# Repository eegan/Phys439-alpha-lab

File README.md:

# Phys439-alpha-lab
Arduino code and KiCAD schematic for McGill PHYS 439 lab setup

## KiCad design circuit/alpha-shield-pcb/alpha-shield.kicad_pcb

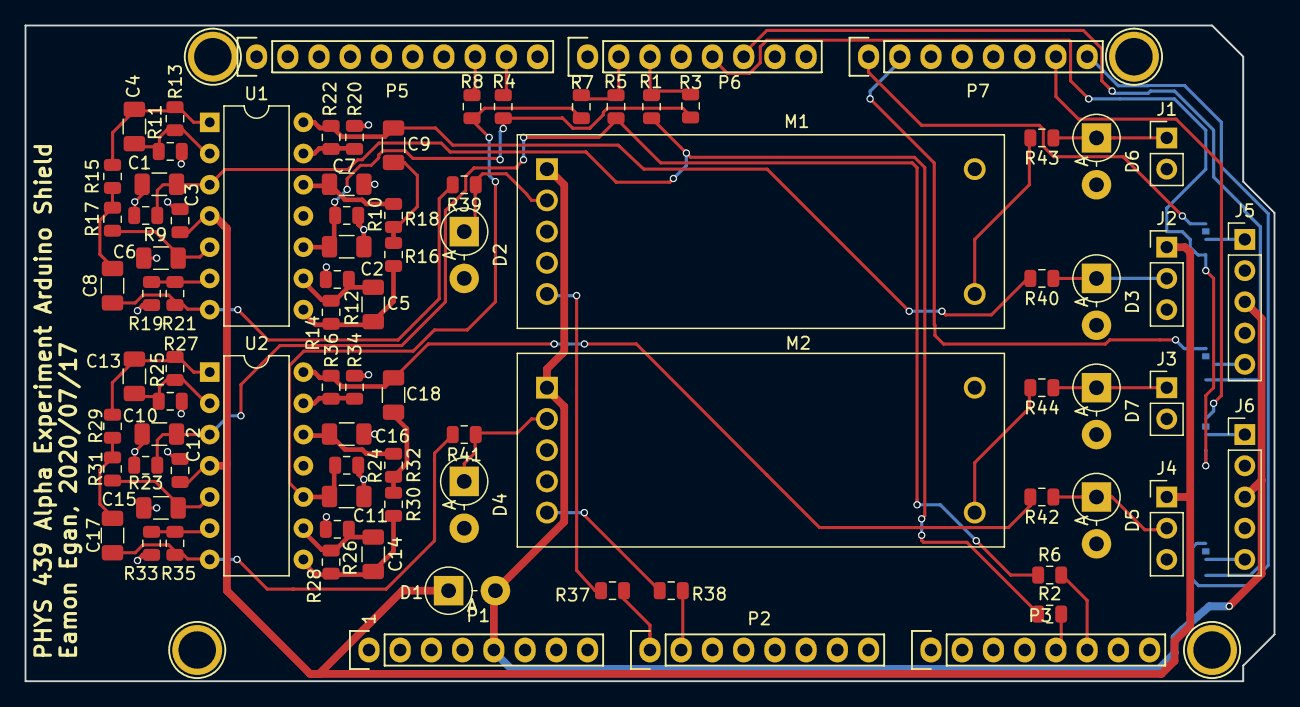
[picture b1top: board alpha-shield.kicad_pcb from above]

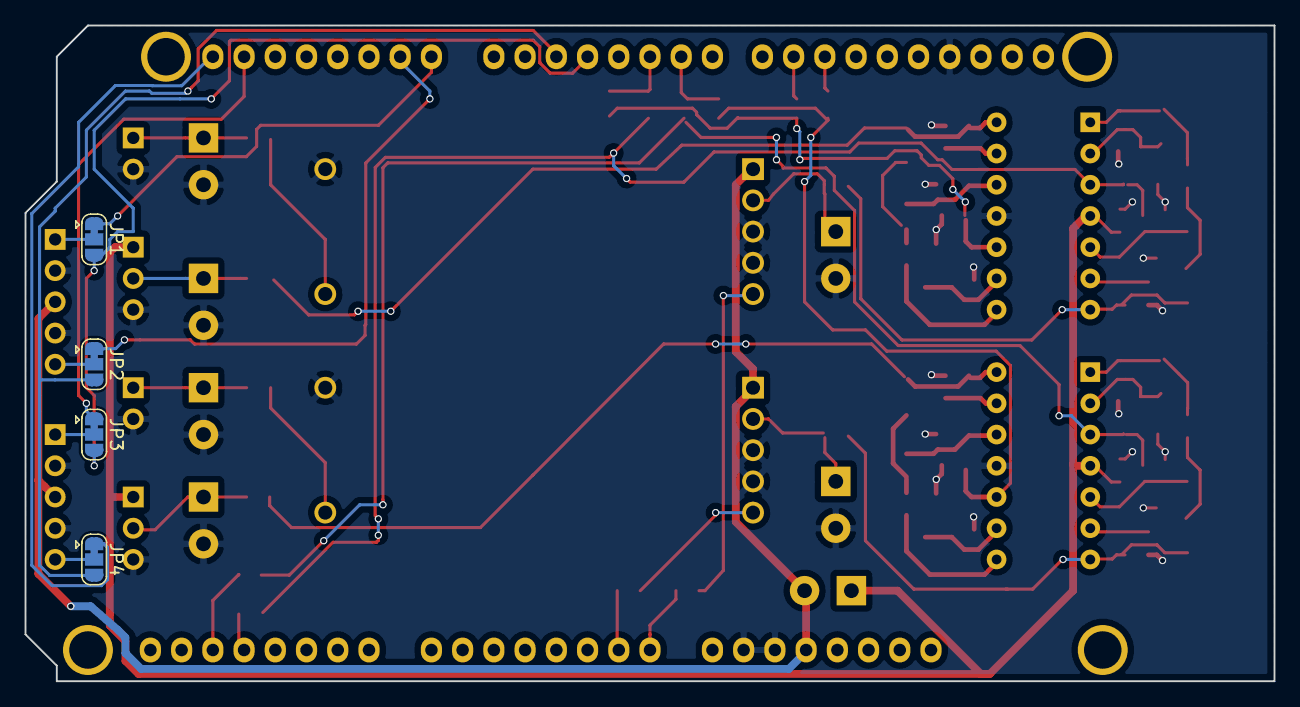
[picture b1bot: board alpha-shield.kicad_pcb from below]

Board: 2 copper layers, 101.6 x 53.3 mm, 93 parts (4 on the bottom side), 59 nets.

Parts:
C1, C2, C4, C5, C6, C7, C8, C9, C10, C11, C13, C14, C15, C16, C17, C18: C; C_1206_3216Metric
C3, C12: C; C_0805_2012Metric
D1: D_ALT; D_DO-15_P3.81mm_Vertical_AnodeUp
D2, D3, D4, D5, D6, D7: D_Zener_ALT; D_DO-15_P3.81mm_Vertical_AnodeUp
J1, J3: Conn_01x02; PinHeader_1x02_P2.54mm_Vertical
J2, J4: Conn_01x03; PinHeader_1x03_P2.54mm_Vertical
J5, J6: Conn_01x05; PinHeader_1x05_P2.54mm_Vertical
JP1, JP2, JP3, JP4: SolderJumper_3_Bridged12; SolderJumper-3_P1.3mm_Bridged12_RoundedPad1.0x1.5mm
M1, M2: AP0vv255x05; ISEG_HV_MODULE
P1: Power; Socket_Strip_Arduino_1x08
P2, P3: Analog; Socket_Strip_Arduino_1x08
P5: PWM; Socket_Strip_Arduino_1x10
P6: PWM; Socket_Strip_Arduino_1x08
P7: Communication; Socket_Strip_Arduino_1x08
P8, P10, P11, P13: CONN_01X01; Arduino_1pin
R1, R2, R3, R4, R5, R6, R7, R8, R9, R10, R11, R12, R13, R14, R15, R16, R17, R18, R19, R20, R21, R22, R23, R24, R25, R26, R27, R28, R29, R30, R31, R32, R33, R34, R35, R36, R37, R38, R39, R40, R41, R42, R43, R44: R_US; R_0805_2012Metric
U1, U2: LT1014; DIP-14_W7.62mm

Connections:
+5V: D1.2, J5.3, J6.3, M1.1, M2.1, P1.5
+24V: C3.2, C12.2, D1.1, J2.1, J4.1, U1.4, U2.4
/2(**): JP2.3, JP4.3, P6.6
/3(**): JP1.3, JP3.3, P6.5
/5(**): P6.3, R1.2, R3.2
/6(**): P6.2, R5.2, R7.2
/9(**): P5.9, R4.2
/10(**): P5.8, R8.2
/14(Tx3): JP1.1, P7.1
/15(Rx3): JP2.1, P7.2
/20(SDA): JP3.1, P7.7
/21(SCL): JP4.1, P7.8
/A0: P2.1, R37.2
/A1: P2.2, R38.2
/DAC0(A12): P3.5, R2.2
/DAC1(A13): P3.6, R6.2
/Sheet5F1ED63A/IN1: C1.2, R1.1, R2.1, R9.2, U1.3
/Sheet5F1ED63A/IN2: C2.2, R3.1, R4.1, R10.2, U1.10
/Sheet5F1ED63A/OUT1: D2.1, M1.2, R39.1
/Sheet5F1ED63A/OUT2: D3.1, J2.2, R40.1
/sheet5F19B79F/IN1: C10.2, R5.1, R6.1, R23.2, U2.3
/sheet5F19B79F/IN2: C11.2, R7.1, R8.1, R24.2, U2.10
/sheet5F19B79F/OUT1: D4.1, M2.2, R41.1
/sheet5F19B79F/OUT2: D5.1, J4.2, R42.1
GND: C1.1, C2.1, C3.1, C6.2, C7.2, C10.1, C11.1, C12.1, C15.2, C16.2, D2.2, D3.2, D4.2, D5.2, D6.2, D7.2, J1.2, J2.3, J3.2, J4.3, J5.2, J5.4, J6.2, J6.4, M1.3, M1.4, M1.7, M2.3, M2.4, M2.7, P1.6, P1.7, P5.4, R9.1, R10.1, R11.2, R12.2, R19.1, R20.1, R23.1, R24.1, R25.2, R26.2, R33.1, R34.1, U1.11, U2.11
unnamed: C4.1, R13.2, R15.2, U1.1
unnamed: C4.2, R11.1, R13.1, U1.2
unnamed: C5.1, R14.2, R16.2, U1.8
unnamed: C5.2, R12.1, R14.1, U1.9
unnamed: C6.1, R17.1, U1.5
unnamed: C7.1, R18.1, U1.12
unnamed: C8.1, R21.1, R39.2, U1.7
unnamed: C8.2, R15.1, R17.2
unnamed: C9.1, R22.1, R40.2, U1.14
unnamed: C9.2, R16.1, R18.2
unnamed: C13.1, R27.2, R29.2, U2.1
unnamed: C13.2, R25.1, R27.1, U2.2
unnamed: C14.1, R28.2, R30.2, U2.8
unnamed: C14.2, R26.1, R28.1, U2.9
unnamed: C15.1, R31.1, U2.5
unnamed: C16.1, R32.1, U2.12
unnamed: C17.1, R35.1, R41.2, U2.7
unnamed: C17.2, R29.1, R31.2
unnamed: C18.1, R36.1, R42.2, U2.14
unnamed: C18.2, R30.1, R32.2
unnamed: D6.1, J1.1, R43.1
unnamed: D7.1, J3.1, R44.1
unnamed: J5.1, JP1.2
unnamed: J5.5, JP2.2
unnamed: J6.1, JP3.2
unnamed: J6.5, JP4.2
unnamed: M1.5, R37.1
unnamed: M1.6, R43.2
unnamed: M2.5, R38.1
unnamed: M2.6, R44.2
unnamed: R19.2, R21.2, U1.6
unnamed: R20.2, R22.2, U1.13
unnamed: R33.2, R35.2, U2.6
unnamed: R34.2, R36.2, U2.13

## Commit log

2020-07-27 Initial commit. (modified) Vreker SCPI parser. Clean compile, not yet tested.
2020-07-30 Adapt it to the Due, use only 12 bit PWMs
2020-08-02 setting calculations fixed to include 3.3V VCC and calculated circuit gains.
2020-08-03 Debug relays
2020-08-03 modify README to reference KiCAD schematic, and move stuff into code folder
2020-08-03 move code down into arduino project-name folder
2020-08-04 Add in offset (get ready for calibration). Put in option for using native serial port.
2020-08-05 Remove debug statements; use programming port
2020-08-05 remove foo.txt
2020-08-05 Add bias control, and approximate offset for valve transistor Vbe
2020-08-07 revise to-do list, fix Dbg (Serial2) reference
2020-08-07 minor cleanup
2020-08-07 playing around with HardwareSerial reference in .cpp file comments in .ino file
2020-08-08 program hanging bug fixed: comment out "Dbg.print" (sent to Serial2)
2020-08-08 Add READ1? READ2? READ3? command, to read A0, A1, A2 pins. READ1 reads the bias voltage monitor pin, READ2 reads a 4:1 divider Values returned should be 12 bit ADC counts.
2020-08-12 Added pressure conversion and pressure readout command
2020-08-14 Add full project including KiCAD design, part data sheets, simulation
2020-08-14 Add revision block, component values, prior to showing board mods
2020-08-14 Add board modifications, update to 1.0a
2020-08-17 Fixed the conversion factor
2020-08-20 Revised serial commands and discontinued getSuffix()
2020-08-20 Minor changes with voltage divider conversion factor
2020-08-26 Added BIAS:ONOFF command
2020-08-26 Fixed ADC voltage readout commands
2020-08-26 Working on PWM commands
2020-08-26 Fixed PWM set commands
2020-08-26 fix pwm raw write, clean up a couple of things
2020-08-26 Add raw PWM readback function
2020-08-26 Fix bug in GetPWM (channel 1 always read back, thanks Megan)
2020-08-27 Fix type conversion in SetPWM (toInt -> toFloat)
2020-08-28 Possible fix for pressure readback issue; will test in lab tomorrow
2020-09-01 increase number of samples averaged; output 5 decimal places
2020-09-24 Extended VOLTAGEn? command to VOLTAGE8 Added VREF:ON, VREF:OFF, VREF:ONOFF 2.5V reference is read between VOLTAGE6 and VOLTAGE7
2021-05-29 Clean up code, remove all other functions Add to-do list
2021-08-08 minor fix
2021-08-10 modify for different voltage range per channel
2021-08-10 fix bug with n_channels in bias readback, set version to 1.1
